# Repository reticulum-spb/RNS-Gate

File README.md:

# RNS-Gate

## Objective

Create a standalone device for access and routing within the Reticulum Network Stack 

## Interfaces for accessing other network nodes

* Integrated:
  - LoRa module (E22/E32 via SPI)
  - WiFi
  - Bluetooth
  - 10/100 Ethernet
* External:
  - RNode (via USB or Bluetooth)
  - WiFi in monitor mode (via USB)
* Audio access and PTT control for connecting analog VHF and HF radios with soft modem implementation 
* Connection of DMR stations via USB (OpenGD77 firmware) 

## Access to user devices

* BlueTooth 
* IP via WiFi and Ethernet

## Implementation

A 3-component "tower":

* Single-board computer based on Orange Pi Zero (both the H2+ and the H3 variant — a single image boots on either)
* Add-on board with an E22/E32 LoRa module 
* Add-on board with an HF/VHF audio interface

## Device configuration

Web interface over IP

## Building with Docker

The build runs inside a container and the working tree is stored
in the named volume `rns-gate-build`. This allows the toolchain, download cache
(`dl/`), and ccache to be reused across builds.

```sh
cd Firmware
./docker-build.sh              # full build -> docker/output/sdcard.img
./docker-build.sh config       # reset .config from defconfig (fast)
./docker-build.sh menuconfig   # edit and export a candidate defconfig
```

`menuconfig` edits the release-specific `.config` in the volume and exports a
minimal defconfig to `docker/output/gate_zero_defconfig`. A full build always
reapplies the defconfig from the repository, so review the exported file first.
To make the changes permanent, use it to replace `system/br2_external/configs/gate_zero_defconfig`.

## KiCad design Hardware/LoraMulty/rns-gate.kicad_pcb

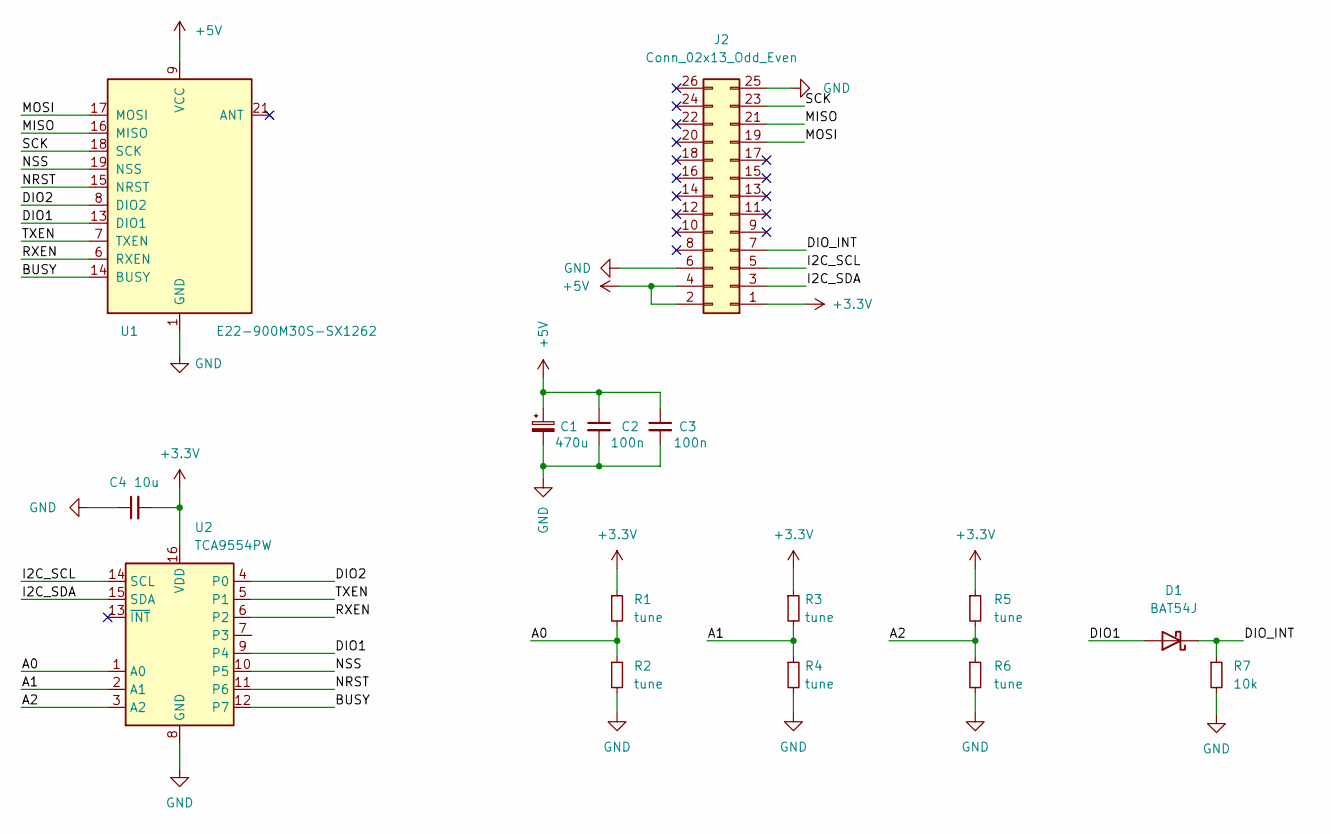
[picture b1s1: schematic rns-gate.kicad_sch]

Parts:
C1: 470u; CP_EIA-7343-43_Kemet-X_Pad2.25x2.55mm_HandSolder
C2, C3: 100n; C_0805_2012Metric_Pad1.18x1.45mm_HandSolder
C4: 10u; C_0805_2012Metric_Pad1.18x1.45mm_HandSolder
D1: BAT54J; D_SOD-323F
J2: Conn_02x13_Odd_Even; PinHeader_2x13_P2.54mm_Vertical
R1, R2, R3, R4, R5, R6: tune; R_0805_2012Metric
R7: 10k; R_0805_2012Metric
U1: E22-900M30S-SX1262
U2: TCA9554PW; TSSOP-16_4.4x5mm_P0.65mm

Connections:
+3.3V: C4.2, J2.1, R1.1, R3.1, R5.1, U2.16 (VDD)
+5V: C1.1, C2.1, C3.1, J2.2, J2.4, U1.9 (VCC), U1.10 (VCC)
/A0: R1.2, R2.1, U2.1 (A0)
/A1: R3.2, R4.1, U2.2 (A1)
/A2: R5.2, R6.1, U2.3 (A2)
/BUSY: U1.14 (BUSY), U2.12 (P7)
/DIO1: D1.2 (A), U1.13 (DIO1), U2.9 (P4)
/DIO2: U1.8 (DIO2), U2.4 (P0)
/DIO_INT: D1.1 (K), J2.7, R7.1
/I2C_SCL: J2.5, U2.14 (SCL)
/I2C_SDA: J2.3, U2.15 (SDA)
/MISO: J2.21, U1.16 (MISO)
/MOSI: J2.19, U1.17 (MOSI)
/NRST: U1.15 (NRST), U2.11 (P6)
/NSS: U1.19 (NSS), U2.10 (P5)
/RXEN: U1.6 (RXEN), U2.6 (P2)
/SCK: J2.23, U1.18 (SCK)
/TXEN: U1.7 (TXEN), U2.5 (P1)
GND: C1.2, C2.2, C3.2, C4.1, J2.6, J2.25, R2.2, R4.2, R6.2, R7.2, U1.1 (GND), U1.2 (GND), U1.3 (GND), U1.4 (GND), U1.5 (GND), U1.11 (GND), U1.12 (GND), U1.20 (GND), U1.22 (GND), U2.8 (GND)

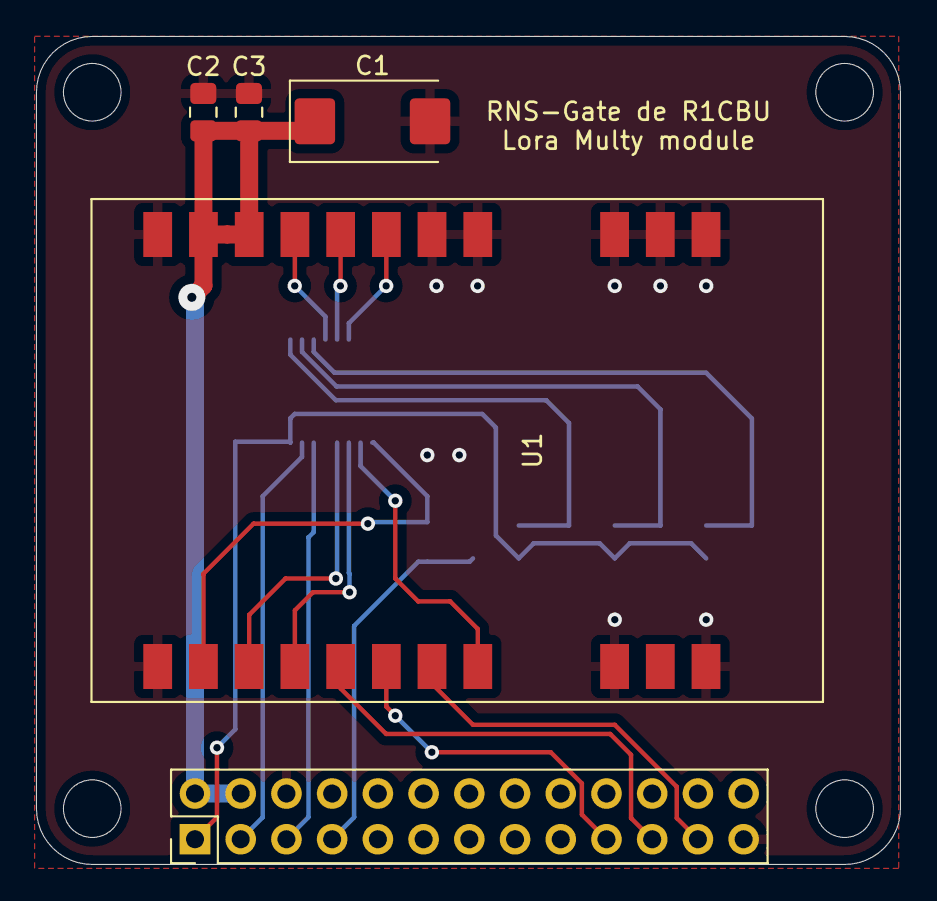
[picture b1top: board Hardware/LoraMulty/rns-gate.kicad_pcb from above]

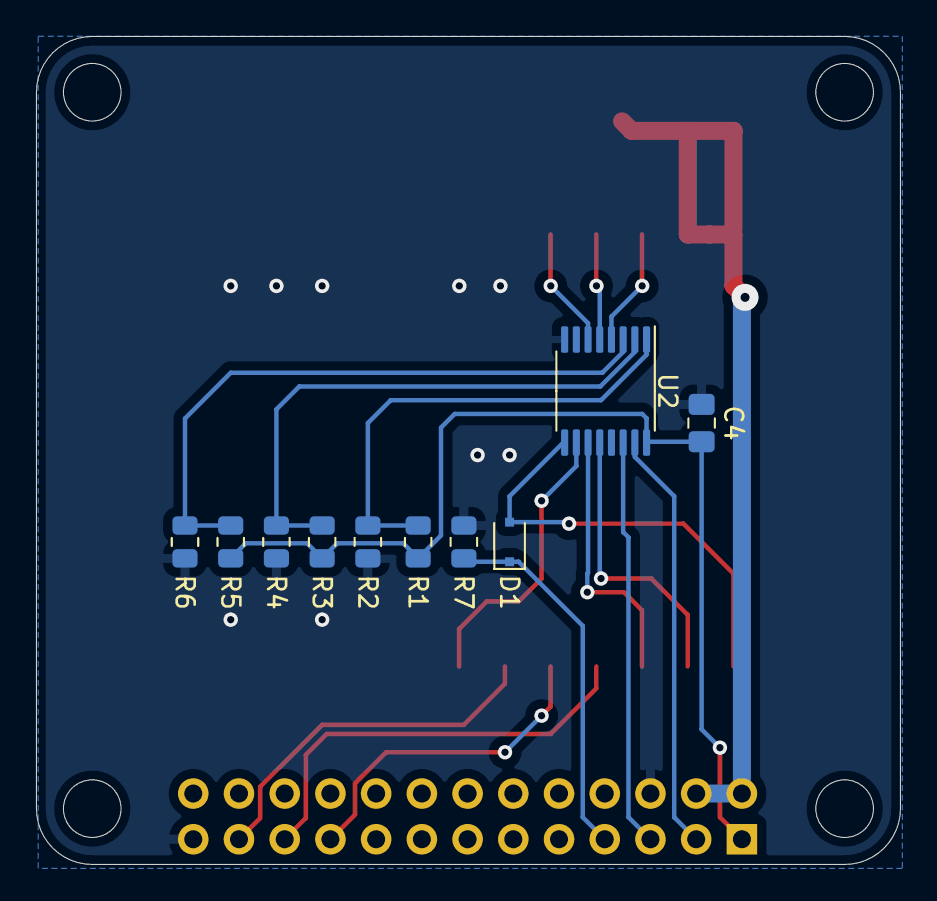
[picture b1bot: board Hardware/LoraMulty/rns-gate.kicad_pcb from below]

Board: 2 copper layers, 48.0 x 46.0 mm, 19 parts (10 on the bottom side), 19 nets.

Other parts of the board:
REF1, REF2, REF3, REF4: MountingHole_3.2mm_M3

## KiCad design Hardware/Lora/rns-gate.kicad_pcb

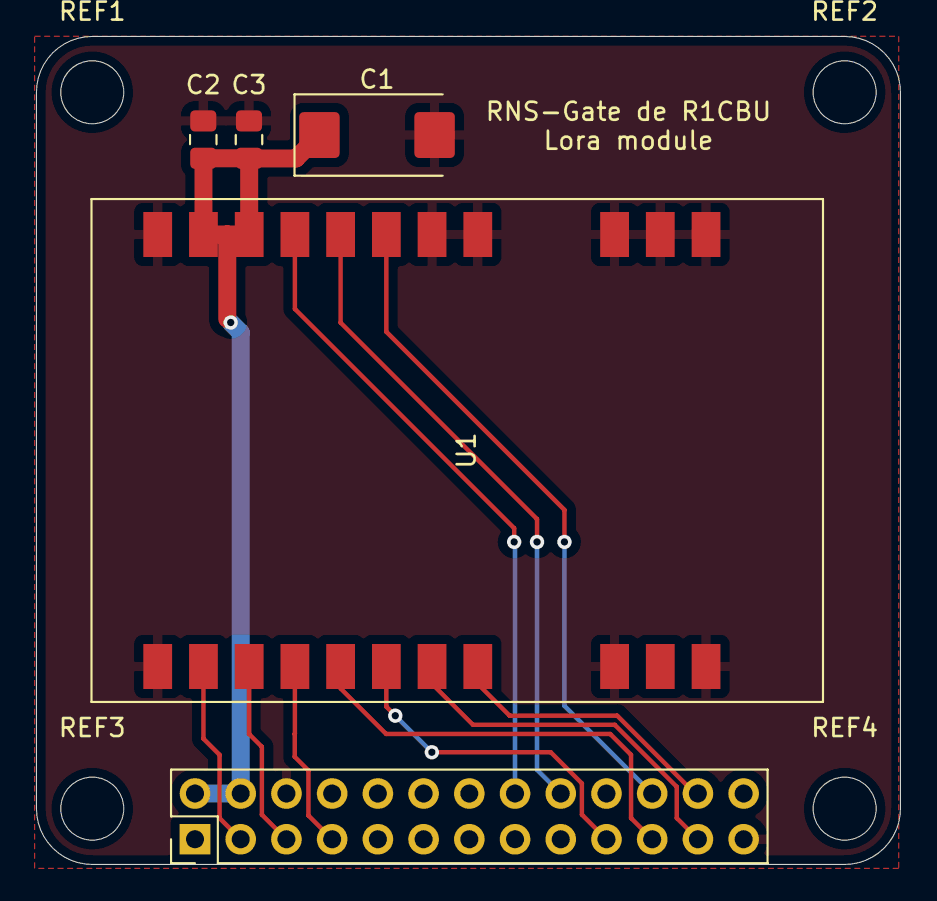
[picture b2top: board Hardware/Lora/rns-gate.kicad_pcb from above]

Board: 2 copper layers, 48.0 x 46.0 mm, 9 parts (0 on the bottom side), 12 nets.

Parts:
C1: C_Polarized_Small; CP_EIA-7343-43_Kemet-X_Pad2.25x2.55mm_HandSolder
C2, C3: C_Small; C_0805_2012Metric_Pad1.18x1.45mm_HandSolder
J2: Conn_02x13_Odd_Even; PinHeader_2x13_P2.54mm_Vertical
REF1, REF2, REF3, REF4: MountingHole_3.5mm
U1: E22-900M30S-SX1262

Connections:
+5V: C1.1, C2.1, C3.1, J2.2, J2.4, U1.9 (VCC), U1.10 (VCC)
/BUSY: J2.5, U1.14 (BUSY)
/DIO1: J2.3, U1.13 (DIO1)
/DIO2: J2.16, U1.8 (DIO2)
/MISO: J2.21, U1.16 (MISO)
/MOSI: J2.19, U1.17 (MOSI)
/NRST: J2.7, U1.15 (NRST)
/NSS: J2.24, U1.19 (NSS)
/RXEN: J2.22, U1.6 (RXEN)
/SCK: J2.23, U1.18 (SCK)
/TXEN: J2.18, U1.7 (TXEN)
GND: C1.2, C2.2, C3.2, J2.6, J2.25, U1.1 (GND), U1.2 (GND), U1.3 (GND), U1.4 (GND), U1.5 (GND), U1.11 (GND), U1.12 (GND), U1.20 (GND), U1.22 (GND)

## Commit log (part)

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2026-06-24 Add Docker-based Buildroot image build
    The image previously had to be built on a Linux host with config.sh. This
    adds a self-contained Docker path so the same gate_zero_defconfig image
    can be produced from macOS without touching the host.
    1. docker/Dockerfile provisions a Debian Buildroot host and a non-root
    build user, since Buildroot refuses to configure several host packages
    as root.
2026-06-24 Tee build output to a visible project-local log
    Build progress was invisible: the container streamed to stdout only, so a
    backgrounded run left no way to follow it and docker/output/ stayed empty
    until the final image copy.
    The wrapper now tees the full Buildroot output to docker/output/build.log,
    giving a predictable path to tail, and prints the grep recipe for the
    package-by-package timeline.
